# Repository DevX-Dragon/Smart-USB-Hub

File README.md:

#  Smart-USB-Hub 
> Because I wanted a hub that actually looks cool and doesn't break.

So, I got tired of those cheap USB hubs that explode after a week lol. I decided to just make my own in KiCad. It’s got a mix of ports because, we’re all living in that annoying "half-USB-A, half-USB-C" era right now. 

## **The Specs**
**4 Ports Total:** Perfectly balanced, as all things should be.

**2x USB-A:** For your mouse, keyboard, or that random flash drive you found.

**2x USB-C:** For the modern stuff (and because flipping the plug 3 times is annoying).

**KiCad Design:** Everything is open sourced. You can build your own version. Or help by contributing

## Layouts

## Renders

> will add blender renders when I have finished my other project

I also like bare PCBs so I can admire them when I use them. I hate 3D designing cases which hides the beauty of the PCB 😭. But if anybody makes a case give a pull request i'll mostly accept and merge it with the main

## **What’s in here?**
**/PCB:** The actual board layout. I tried to keep it clean so it's easy to solder.

**/Schematic:** The "brain" map. Check it out if you want to see how the power flows.

**/production:** Necassary files to order your own PCB!

## **How to make one**
Order the Boards: Grab the Gerber files and send them to JLCPCB or PCBWay (or wherever you get your fix).

Buy the Parts: Check the BOM (Bill of Materials). Don't cheap out on the capacitors!

Solder it: Get your iron hot, put on some music, and try not to bridge the tiny pins on the USB-C ports (those things are a pain, honestly).

Plug it in: If it doesn't smoke, you did it!

## BOM Base
> The xlsx is also in the root directory

If you're building this yourself, here is what you need to buy. I got my small parts from [duino.lk](https://www.duino.lk). Which is a local-only for Sri Lanka. These components are THT which are easy to solder by yourself :D. Other components were ordered w/ PCBA.

| Product Name | Quantity | Source Link | Price (USD) |
| :--- | :---: | :--- | :--- |
| 220uF 16v Aluminum Electrolytic Capacitor | 8 | [duino.lk](https://www.duino.lk/product/220uf-16v-aluminum-electrolytic-capacitor/) | $0.40 |
| 10uF 25v Aluminum Electrolytic Capacitor | 8 | [duino.lk](https://www.duino.lk/product/10uf-25v-aluminum-electrolytic-capacitor/) | $0.25 |
| 104PF 0.1UF Ceramic Capacitor Disc | 20 | [duino.lk](https://www.duino.lk/product/104pf-0-1uf-ceramic-capacitor-disc/) | $0.20 |
| 1UF 50V Aluminum Electrolytic Capacitor | 4 | [duino.lk](https://www.duino.lk/product/1uf-50v-aluminum-electrolytic-capacitor/) | $0.15 |
| PCB (PCB + PCBA + SHIPPING) | 5 | JLC PCB | $78.00 |
| **Shipping (for duino.lk)** | - | - | $2.00 |
| **Exchange Tax?** | - | - | $5.00 |
| **Total** | | | **$86.00** |

## ** Disclaimer**
If you solder something backwards and it smells like burning plastic... that's on you, bro. Double-check your polarity!

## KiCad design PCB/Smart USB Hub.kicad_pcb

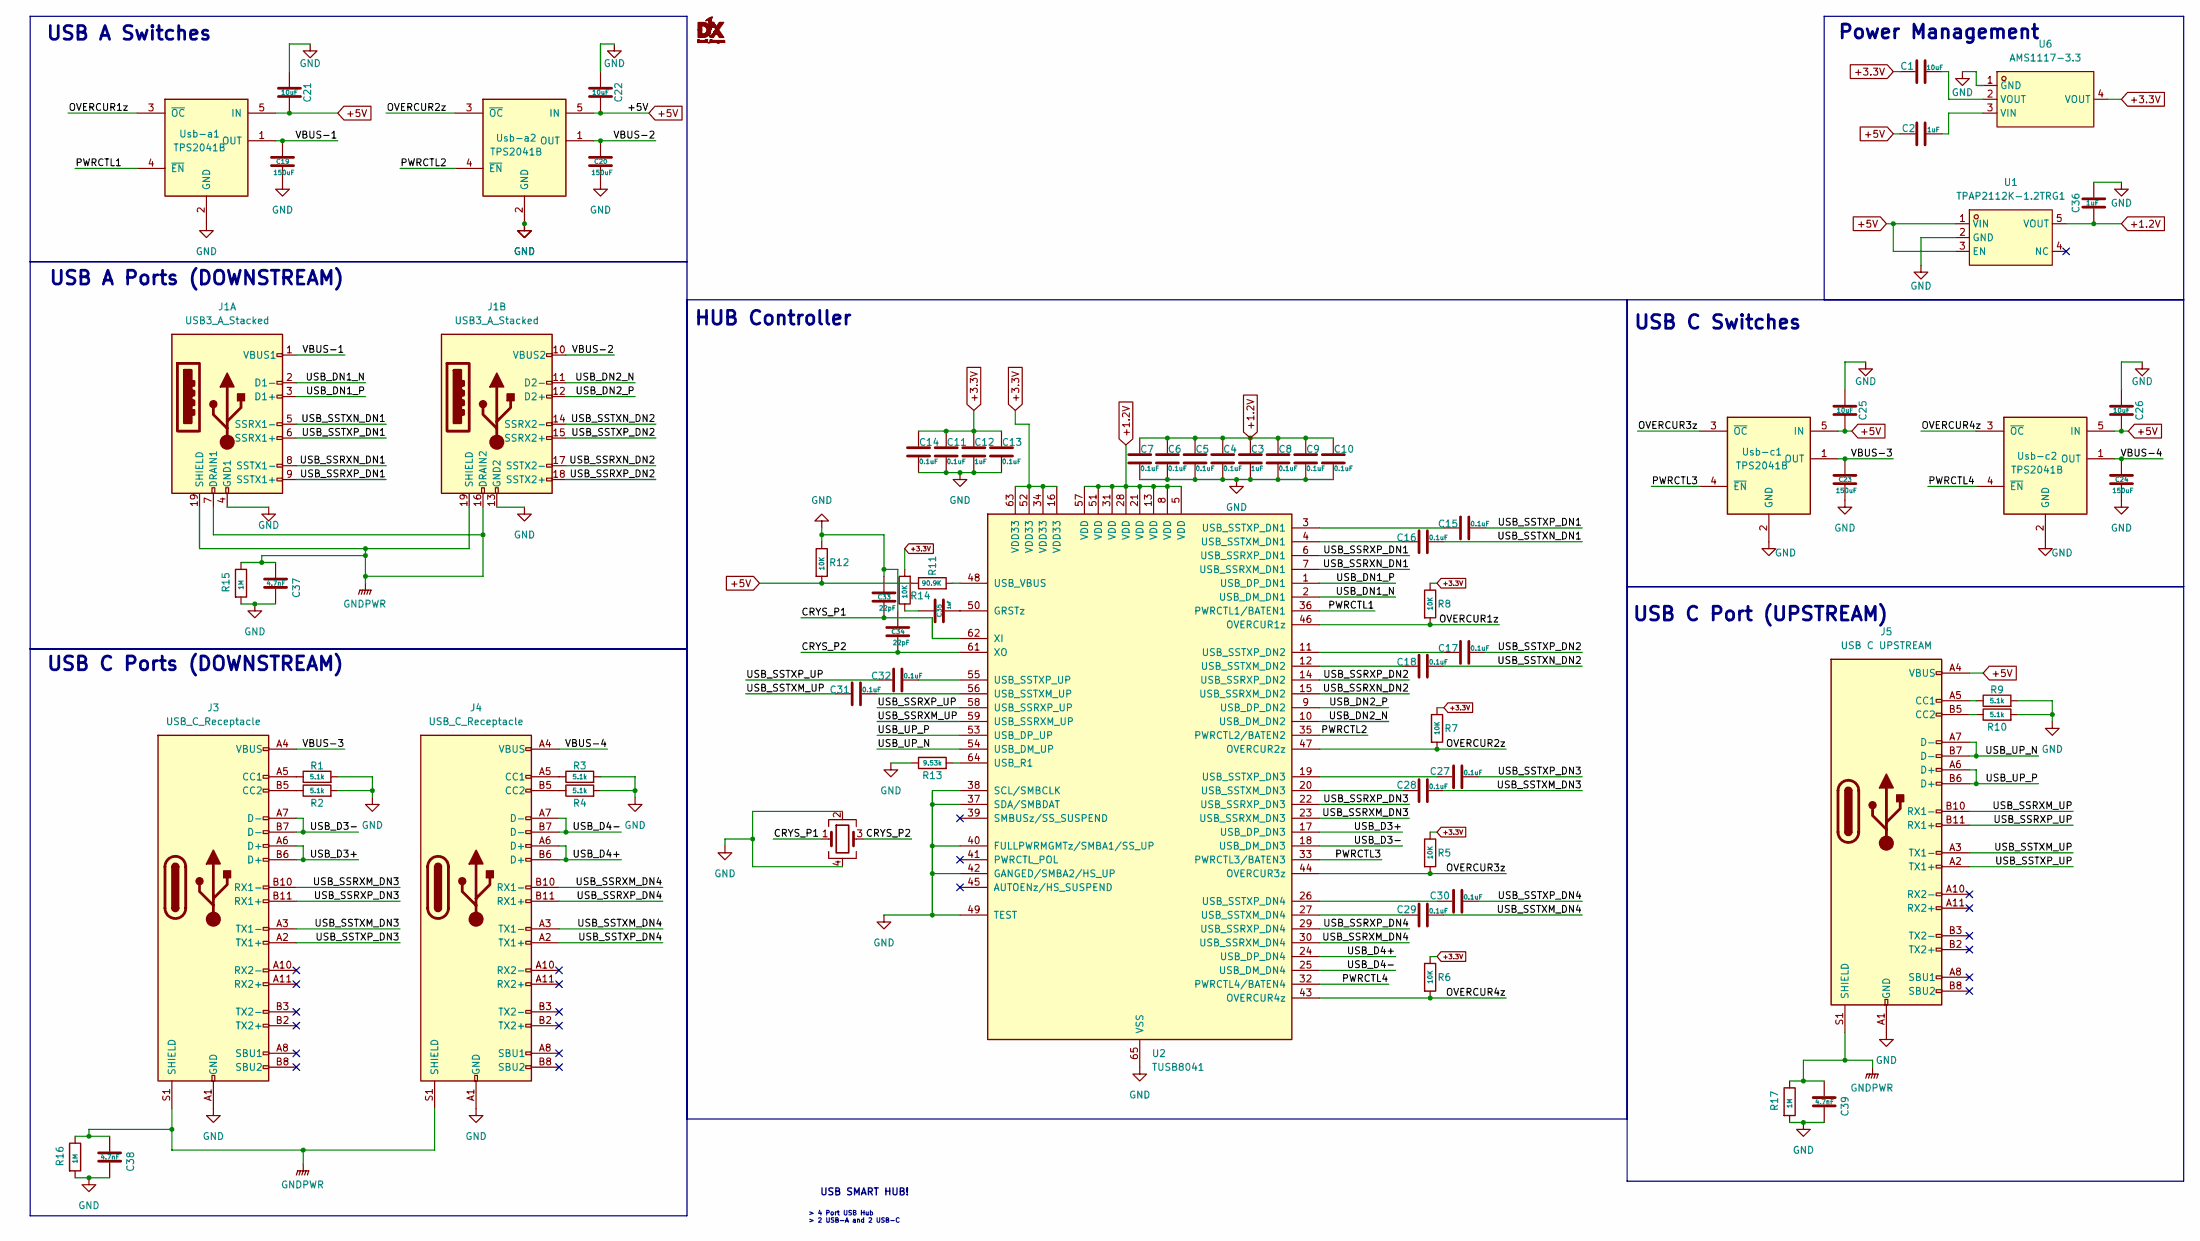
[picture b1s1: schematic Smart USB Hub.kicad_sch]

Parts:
C1: 10uF; C_0805_2012Metric_Pad1.15x1.40mm_HandSolder
C2, C3: 1uF; C_0805_2012Metric_Pad1.15x1.40mm_HandSolder
C4, C5, C6, C7, C8, C9, C10, C11, C13, C14: 0.1uF; C_0603_1608Metric_Pad1.08x0.95mm_HandSolder
C12: 1uF; C_0603_1608Metric_Pad1.08x0.95mm_HandSolder
C15, C16, C17, C18, C27, C28, C29, C30, C31, C32: 0.1uF; C_Disc_D5.0mm_W2.5mm_P5.00mm
C19, C20, C23, C24: 150uF; CP_Radial_D6.3mm_P2.50mm
C21, C22, C25, C26: 10uF; CP_Radial_D5.0mm_P2.00mm
C33, C34: 22pF; C_0603_1608Metric_Pad1.08x0.95mm_HandSolder
C35, C36: 1uF; C_Disc_D5.0mm_W2.5mm_P5.00mm
C37, C38, C39: 4.7nF; C_0603_1608Metric_Pad1.08x0.95mm_HandSolder
J1: USB3_A_Stacked; USB3_A_Molex_48406-0001_Horizontal_Stacked
J3, J4: USB_C_Receptacle; USB_C_Receptacle_Molex_105450-0101
J5: USB C UPSTREAM; USB_C_Receptacle_Molex_105450-0101
R1, R2, R3, R4, R9, R10: 5.1k; R_0603_1608Metric_Pad0.98x0.95mm_HandSolder
R5, R6, R7, R8, R12, R14: 10K; R_0603_1608Metric_Pad0.98x0.95mm_HandSolder
R11: 90.9K; R_0603_1608Metric_Pad0.98x0.95mm_HandSolder
R13: 9.53k; R_0603_1608Metric_Pad0.98x0.95mm_HandSolder
R15, R16, R17: 1M; R_0603_1608Metric_Pad0.98x0.95mm_HandSolder
U1: TPAP2112K-1.2TRG1; SOT-23-5_HandSoldering; LCSC Part C49451994
U2: TUSB8041; QFN-64-1EP_9x9mm_P0.5mm_EP6x6mm_ThermalVias
U6: AMS1117-3.3; SOT-223; LCSC Part C6186
Usb-a1, Usb-a2: TPS2041B; SOT-23-5_HandSoldering
Usb-c1, Usb-c2: TPS2041B; SOT-23-5_HandSoldering
Y1: Crystal_GND24; Crystal_SMD_3225-4Pin_3.2x2.5mm

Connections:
+1.2V: C3.1, C4.1, C5.1, C6.1, C7.1, C8.1, C9.1, C10.1, C36.1, U1.5 (VOUT), U2.5 (VDD), U2.8 (VDD), U2.13 (VDD), U2.21 (VDD), U2.28 (VDD), U2.31 (VDD), U2.51 (VDD), U2.57 (VDD)
+3.3V: C1.1, C11.1, C12.1, C13.1, C14.1, R5.1, R6.1, R7.1, R8.1, R14.2, U2.16 (VDD33), U2.34 (VDD33), U2.52 (VDD33), U2.63 (VDD33), U6.4 (VOUT)
+5V: C2.1, C21.2, C22.2, C25.2, C26.2, J5.A4 (VBUS), J5.A9 (VBUS), J5.B4 (VBUS), J5.B9 (VBUS), R11.1, R12.2, U1.1 (VIN), U1.3 (EN), Usb-a1.5 (IN), Usb-a2.5 (IN), Usb-c1.5 (IN), Usb-c2.5 (IN)
/CRYS_P1: C33.2, U2.62 (XI), Y1.1
/CRYS_P2: C34.2, U2.61 (XO), Y1.3
/OVERCUR1z: R8.2, U2.46 (OVERCUR1z), Usb-a1.3 (~OC)
/OVERCUR2z: R7.2, U2.47 (OVERCUR2z), Usb-a2.3 (~OC)
/OVERCUR3z: R5.2, U2.44 (OVERCUR3z), Usb-c1.3 (~OC)
/OVERCUR4z: R6.2, U2.43 (OVERCUR4z), Usb-c2.3 (~OC)
/PWRCTL1: U2.36 (PWRCTL1/BATEN1), Usb-a1.4 (~EN)
/PWRCTL2: U2.35 (PWRCTL2/BATEN2), Usb-a2.4 (~EN)
/PWRCTL3: U2.33 (PWRCTL3/BATEN3), Usb-c1.4 (~EN)
/PWRCTL4: U2.32 (PWRCTL4/BATEN4), Usb-c2.4 (~EN)
/USB_D3+: J3.A6 (D+), J3.B6 (D+), U2.17 (USB_DP_DN3)
/USB_D3-: J3.A7 (D-), J3.B7 (D-), U2.18 (USB_DM_DN3)
/USB_D4+: J4.A6 (D+), J4.B6 (D+), U2.24 (USB_DP_DN4)
/USB_D4-: J4.A7 (D-), J4.B7 (D-), U2.25 (USB_DM_DN4)
/USB_DN1_N: J1.2 (D1-), U2.2 (USB_DM_DN1)
/USB_DN1_P: J1.3 (D1+), U2.1 (USB_DP_DN1)
/USB_DN2_N: J1.11 (D2-), U2.10 (USB_DM_DN2)
/USB_DN2_P: J1.12 (D2+), U2.9 (USB_DP_DN2)
/USB_SSRXM_DN3: J3.B10 (RX1-), U2.23 (USB_SSRXM_DN3)
/USB_SSRXM_DN4: J4.B10 (RX1-), U2.30 (USB_SSRXM_DN4)
/USB_SSRXM_UP: J5.B10 (RX1-), U2.59 (USB_SSRXM_UP)
/USB_SSRXN_DN1: J1.8 (SSTX1-), U2.7 (USB_SSRXM_DN1)
/USB_SSRXN_DN2: J1.17 (SSTX2-), U2.15 (USB_SSRXM_DN2)
/USB_SSRXP_DN1: J1.9 (SSTX1+), U2.6 (USB_SSRXP_DN1)
/USB_SSRXP_DN2: J1.18 (SSTX2+), U2.14 (USB_SSRXP_DN2)
/USB_SSRXP_DN3: J3.B11 (RX1+), U2.22 (USB_SSRXP_DN3)
/USB_SSRXP_DN4: J4.B11 (RX1+), U2.29 (USB_SSRXP_DN4)
/USB_SSRXP_UP: J5.B11 (RX1+), U2.58 (USB_SSRXP_UP)
/USB_SSTXM_DN3: C28.2, J3.A3 (TX1-)
/USB_SSTXM_DN4: C29.2, J4.A3 (TX1-)
/USB_SSTXM_UP: C31.1, J5.A3 (TX1-)
/USB_SSTXN_DN1: C16.2, J1.5 (SSRX1-)
/USB_SSTXN_DN2: C18.2, J1.14 (SSRX2-)
/USB_SSTXP_DN1: C15.2, J1.6 (SSRX1+)
/USB_SSTXP_DN2: C17.2, J1.15 (SSRX2+)
/USB_SSTXP_DN3: C27.2, J3.A2 (TX1+)
/USB_SSTXP_DN4: C30.2, J4.A2 (TX1+)
/USB_SSTXP_UP: C32.1, J5.A2 (TX1+)
/USB_UP_N: J5.A7 (D-), J5.B7 (D-), U2.54 (USB_DM_UP)
/USB_UP_P: J5.A6 (D+), J5.B6 (D+), U2.53 (USB_DP_UP)
/VBUS-1: C19.1, J1.1 (VBUS1), Usb-a1.1 (OUT)
/VBUS-2: C20.1, J1.10 (VBUS2), Usb-a2.1 (OUT)
/VBUS-3: C23.1, J3.A4 (VBUS), J3.A9 (VBUS), J3.B4 (VBUS), J3.B9 (VBUS), Usb-c1.1 (OUT)
/VBUS-4: C24.1, J4.A4 (VBUS), J4.A9 (VBUS), J4.B4 (VBUS), J4.B9 (VBUS), Usb-c2.1 (OUT)
GND: C3.2, C4.2, C5.2, C6.2, C7.2, C8.2, C9.2, C10.2, C11.2, C12.2, C13.2, C14.2, C19.2, C20.2, C21.1, C22.1, C23.2, C24.2, C25.1, C26.1, C33.1, C34.1, C36.2, C37.2, C38.2, C39.2, J1.4 (GND1), J1.13 (GND2), J3.A1 (GND), J3.A12 (GND), J3.B1 (GND), J3.B12 (GND), J4.A1 (GND), J4.A12 (GND), J4.B1 (GND), J4.B12 (GND), J5.A1 (GND), J5.A12 (GND), J5.B1 (GND), J5.B12 (GND), R1.2, R2.2, R3.2, R4.2, R9.2, R10.2, R12.1, R13.1, R15.2, R16.2, R17.2, U1.2 (GND), U2.37 (SDA/SMBDAT), U2.38 (SCL/SMBCLK), U2.40 (FULLPWRMGMTz/SMBA1/SS_UP), U2.42 (GANGED/SMBA2/HS_UP), U2.49 (TEST), U2.65 (VSS), U6.1 (GND), Usb-a1.2 (GND), Usb-a2.2 (GND), Usb-c1.2 (GND), Usb-c2.2 (GND), Y1.2, Y1.4
GNDPWR: C37.1, C38.1, C39.1, J1.7 (DRAIN1), J1.16 (DRAIN2), J1.19 (SHIELD), J3.S1 (SHIELD), J4.S1 (SHIELD), J5.S1 (SHIELD), R15.1, R16.1, R17.1
unnamed: C1.2, U6.2 (VOUT)
unnamed: C35.1, R14.1
unnamed: J3.A5 (CC1), R1.1
unnamed: J3.B5 (CC2), R2.1
unnamed: J4.A5 (CC1), R3.1
unnamed: J4.B5 (CC2), R4.1
unnamed: J5.A5 (CC1), R9.1
unnamed: J5.B5 (CC2), R10.1
unnamed: C35.2, U2.50 (GRSTz)
unnamed: R13.2, U2.64 (USB_R1)
unnamed: C16.1, U2.4 (USB_SSTXM_DN1)
unnamed: C18.1, U2.12 (USB_SSTXM_DN2)
unnamed: C28.1, U2.20 (USB_SSTXM_DN3)
unnamed: C29.1, U2.27 (USB_SSTXM_DN4)
unnamed: C31.2, U2.56 (USB_SSTXM_UP)
unnamed: C15.1, U2.3 (USB_SSTXP_DN1)
unnamed: C17.1, U2.11 (USB_SSTXP_DN2)
unnamed: C27.1, U2.19 (USB_SSTXP_DN3)
unnamed: C30.1, U2.26 (USB_SSTXP_DN4)
unnamed: C32.2, U2.55 (USB_SSTXP_UP)
unnamed: R11.2, U2.48 (USB_VBUS)
unnamed: C2.2, U6.3 (VIN)

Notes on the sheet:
USB SMART HUB!
USB A Switches
USB C Ports (DOWNSTREAM)
Power Management
> 4 Port USB Hub > 2 USB-A and 2 USB-C
USB C Switches
USB C Port (UPSTREAM)
USB A Ports (DOWNSTREAM)
HUB Controller

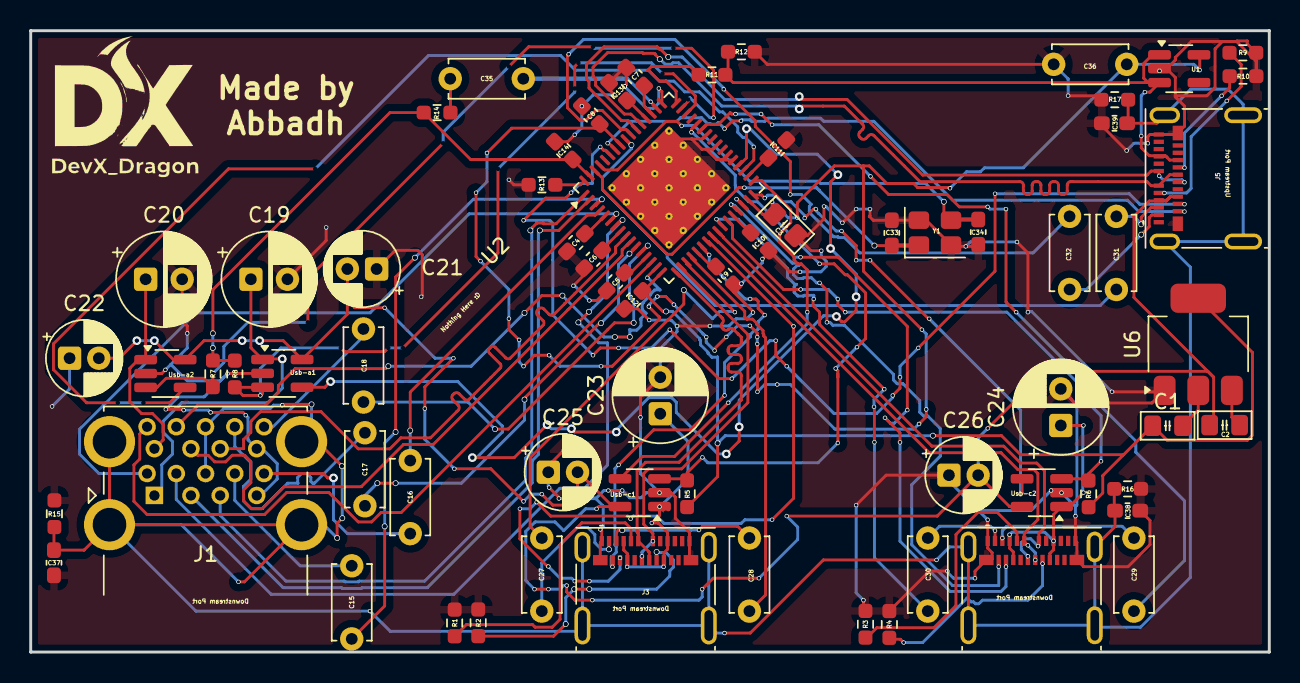
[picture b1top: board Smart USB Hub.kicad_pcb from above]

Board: 2 copper layers, 84.7 x 42.5 mm, 68 parts (0 on the bottom side), 71 nets.

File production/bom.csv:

Designator,Footprint,Quantity,Value,LCSC Part #
C1,0805,1,10uF,
"C10, C11, C13, C14, C4, C5, C6, C7, C8, C9",0603,10,0.1uF,
C12,0603,1,1uF,
"C15, C16, C17, C18, C27, C28, C29, C30, C31, C32",C_Disc_D5.0mm_W2.5mm_P5.00mm,10,0.1uF,
"C19, C20, C23, C24",CP_Radial_D6.3mm_P2.50mm,4,150uF,
"C2, C3",0805,2,1uF,
"C21, C22, C25, C26",CP_Radial_D5.0mm_P2.00mm,4,10uF,
"C33, C34",0603,2,22pF,
"C35, C36",C_Disc_D5.0mm_W2.5mm_P5.00mm,2,1uF,
"C37, C38, C39",0603,3,4.7nF,
J1,USB3_A_Molex_48406-0001_Horizontal_Stacked,1,USB3_A_Stacked,
"J3, J4",USB_C_Receptacle_Molex_105450-0101,2,USB_C_Receptacle,
J5,USB_C_Receptacle_Molex_105450-0101,1,USB C UPSTREAM,
"R1, R10, R2, R3, R4, R9",0603,6,5.1k,
R11,0603,1,90.9K,
"R12, R14, R5, R6, R7, R8",0603,6,10K,
R13,0603,1,9.53k,
"R15, R16, R17",0603,3,1M,
U1,SOT-23-5_HandSoldering,1,TPAP2112K-1.2TRG1,C49451994
U2,QFN-64-1EP_9x9mm_P0.5mm_EP6x6mm_ThermalVias,1,TUSB8041,
U6,SOT-223,1,AMS1117-3.3,C6186
"USB-A1, USB-A2, USB-C1, USB-C2",SOT-23-5_HandSoldering,4,TPS2041B,
Y1,Crystal_SMD_3225-4Pin_3.2x2.5mm,1,Crystal_GND24,

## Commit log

2026-02-15 Adding Schematics v1
2026-02-15 Adding PCB Files v1
2026-02-15 Adding Production Files v1
2026-02-15 Random Images
    Will add blender renders later :3
2026-02-15 Update README.md v1
2026-02-15 Uploading BOM to root v1
